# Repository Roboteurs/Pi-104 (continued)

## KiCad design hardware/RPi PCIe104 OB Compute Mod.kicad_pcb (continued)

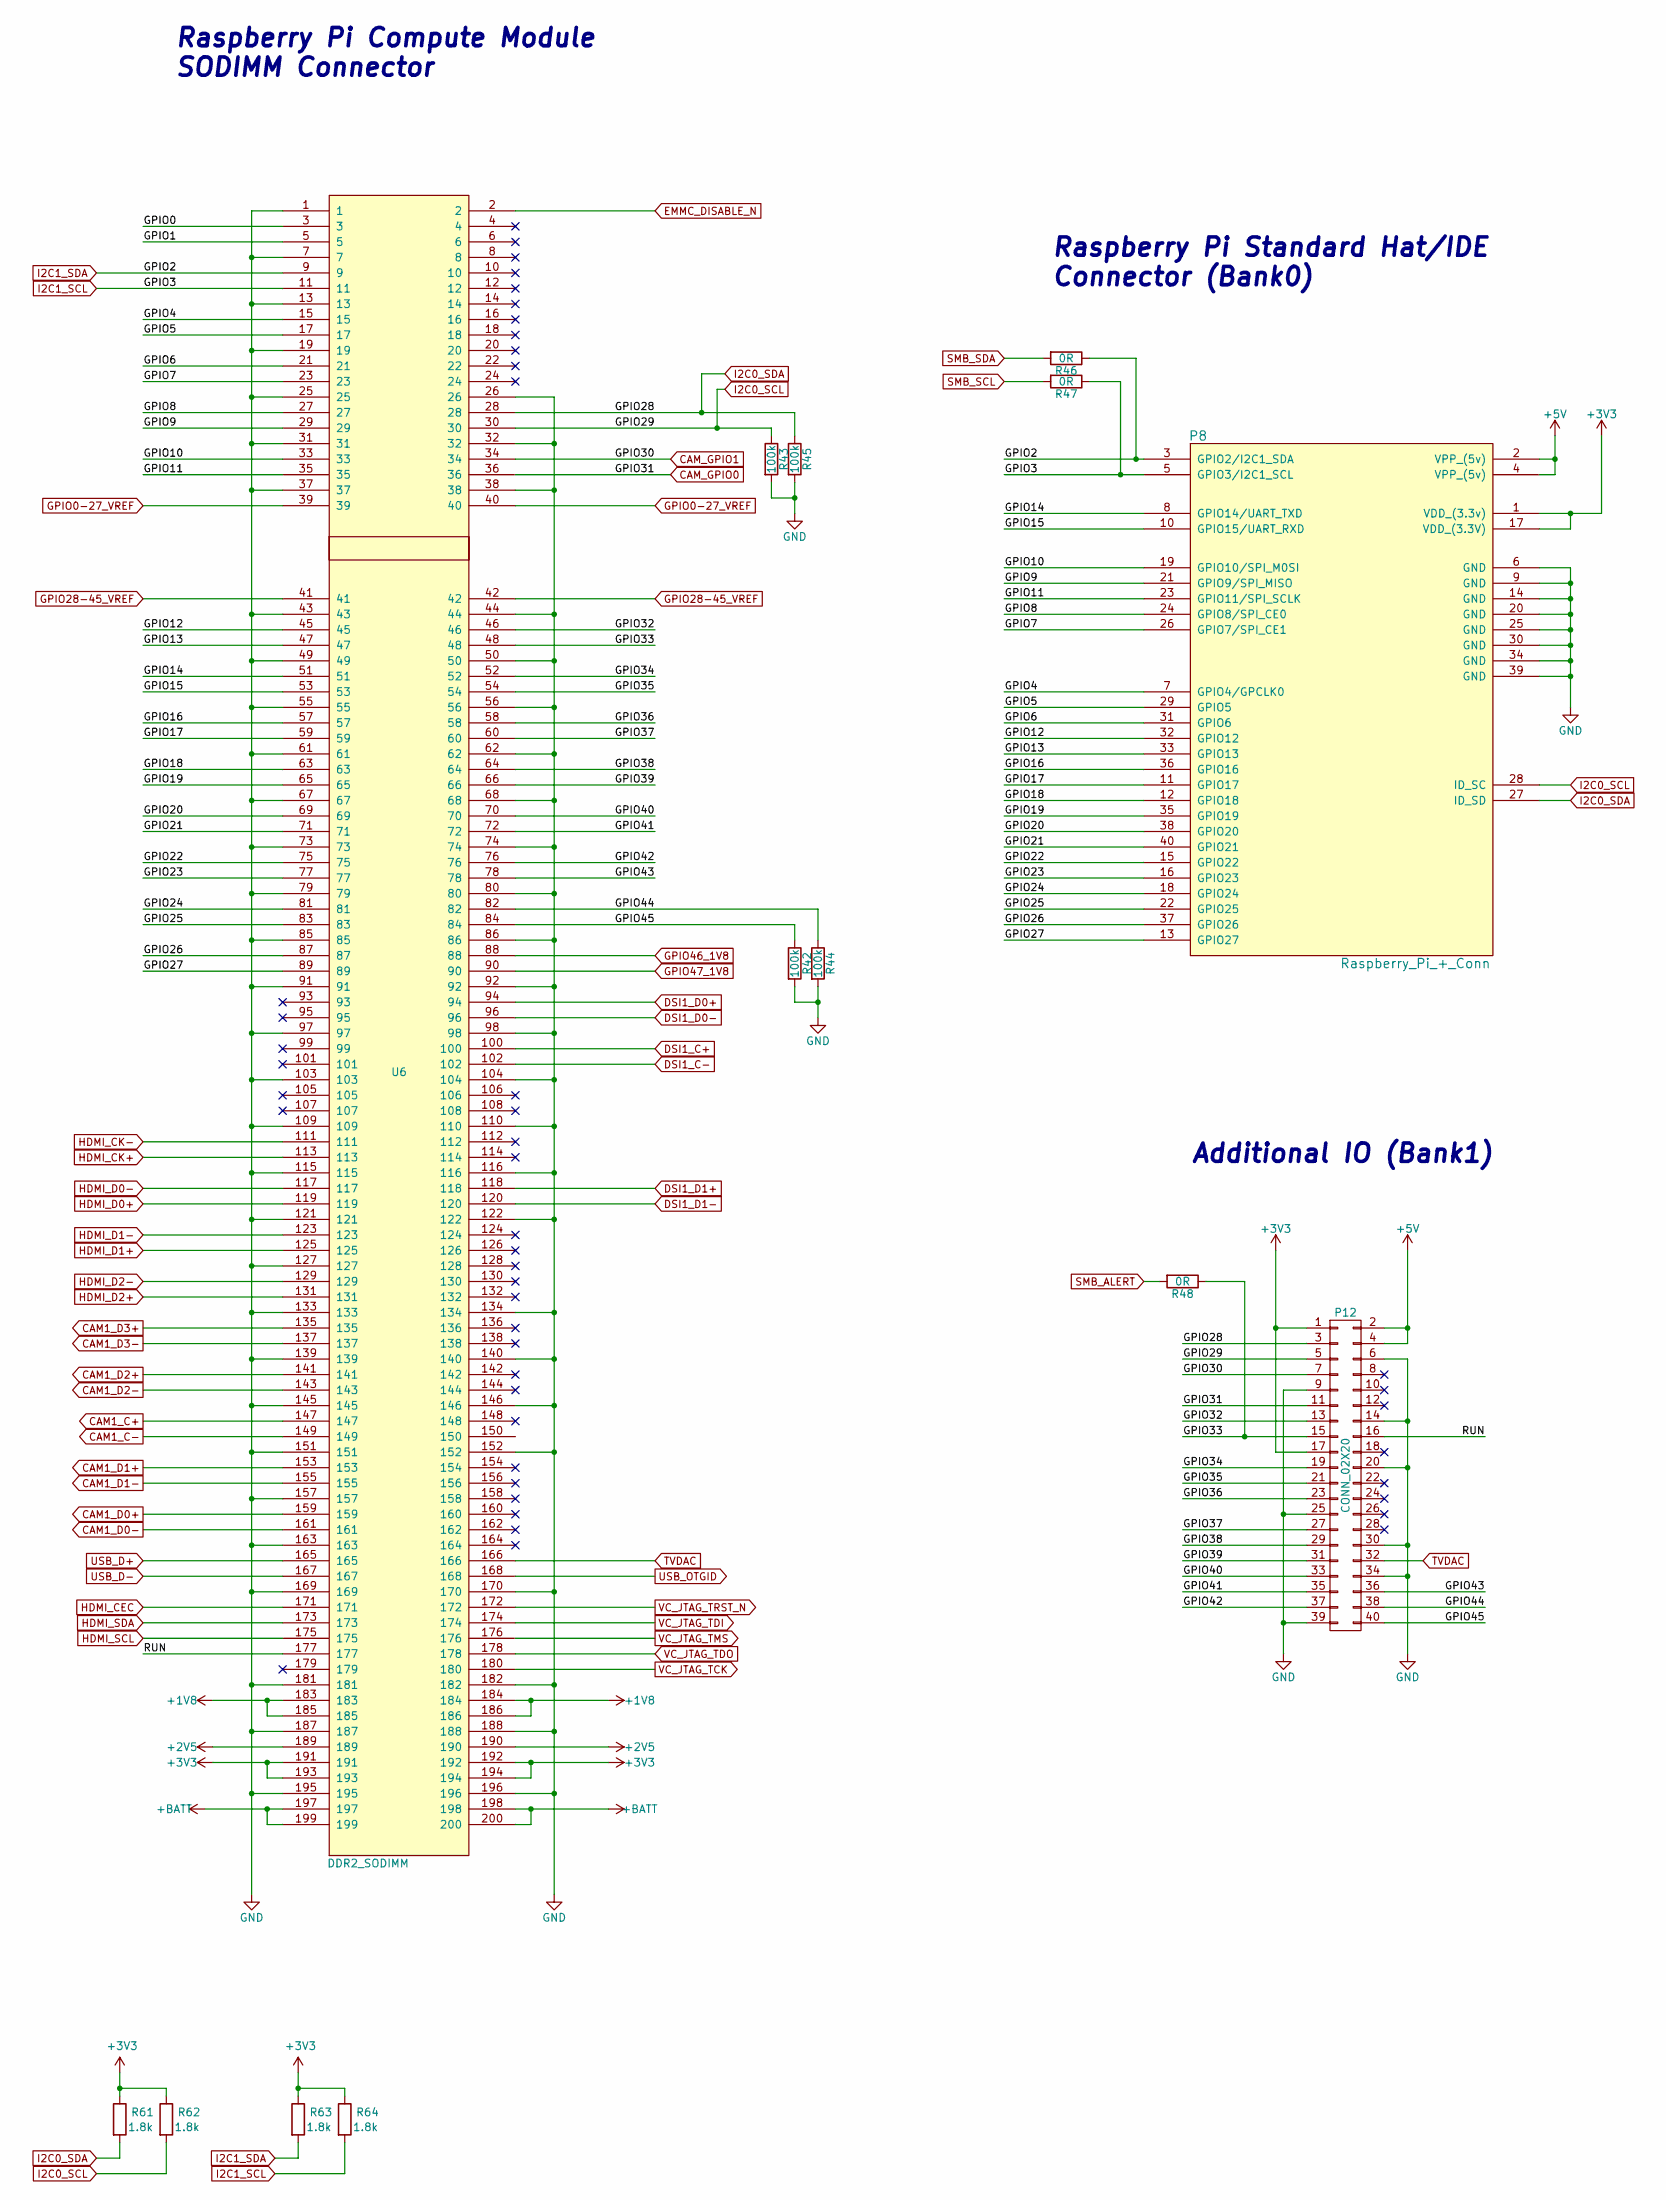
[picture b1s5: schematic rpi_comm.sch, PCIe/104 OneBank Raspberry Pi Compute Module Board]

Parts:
P8: Raspberry_Pi_+_Conn; vasch_strip_20x2; mouser# 517-N2540-6002RB
P12: CONN_02X20; vasch_strip_20x2; mouser# 517-N2540-6002RB
R42, R43, R44, R45: 100k; r_0402; mouser# 667-ERJ-2GEJ104X
R46, R47, R48: 0R; r_0402; mouser# 71-CRCW0402-0-E3
R61, R62, R63, R64: 1.8k; r_0402; mouser# 667-ERJ-2GEJ182X
U6: DDR2_SODIMM; Socket_SODIMM_DDR1-2_TE_1612618_Debug; mouser# 571-1612618-4

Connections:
+1V8: U6.183, U6.184, U6.185, U6.186; also elsewhere on the board
+2V5: U6.189, U6.190; also elsewhere on the board
+3V3: P8.1 (VDD_(3.3v)), P8.17 (VDD_(3.3V)), P12.1, P12.17, R61.1, R62.1, R63.1, R64.1, U6.191, U6.192, U6.193, U6.194; also elsewhere on the board
+5V: P8.2 (VPP_(5v)), P8.4 (VPP_(5v)), P12.2, P12.4; also elsewhere on the board
+BATT: U6.197, U6.198, U6.199, U6.200; also elsewhere on the board
/Raspberry Pi Mod & I/O/GPIO0: U6.3
/Raspberry Pi Mod & I/O/GPIO1: U6.5
/Raspberry Pi Mod & I/O/GPIO4: P8.7 (GPIO4/GPCLK0), U6.15
/Raspberry Pi Mod & I/O/GPIO5: P8.29 (GPIO5), U6.17
/Raspberry Pi Mod & I/O/GPIO6: P8.31 (GPIO6), U6.21
/Raspberry Pi Mod & I/O/GPIO7: P8.26 (GPIO7/SPI_CE1), U6.23
/Raspberry Pi Mod & I/O/GPIO8: P8.24 (GPIO8/SPI_CE0), U6.27
/Raspberry Pi Mod & I/O/GPIO9: P8.21 (GPIO9/SPI_MISO), U6.29
/Raspberry Pi Mod & I/O/GPIO10: P8.19 (GPIO10/SPI_M0SI), U6.33
/Raspberry Pi Mod & I/O/GPIO11: P8.23 (GPIO11/SPI_SCLK), U6.35
/Raspberry Pi Mod & I/O/GPIO12: P8.32 (GPIO12), U6.45
/Raspberry Pi Mod & I/O/GPIO13: P8.33 (GPIO13), U6.47
/Raspberry Pi Mod & I/O/GPIO14: P8.8 (GPIO14/UART_TXD), U6.51
/Raspberry Pi Mod & I/O/GPIO15: P8.10 (GPIO15/UART_RXD), U6.53
/Raspberry Pi Mod & I/O/GPIO16: P8.36 (GPIO16), U6.57
/Raspberry Pi Mod & I/O/GPIO17: P8.11 (GPIO17), U6.59
/Raspberry Pi Mod & I/O/GPIO18: P8.12 (GPIO18), U6.63
/Raspberry Pi Mod & I/O/GPIO19: P8.35 (GPIO19), U6.65
/Raspberry Pi Mod & I/O/GPIO20: P8.38 (GPIO20), U6.69
/Raspberry Pi Mod & I/O/GPIO21: P8.40 (GPIO21), U6.71
/Raspberry Pi Mod & I/O/GPIO22: P8.15 (GPIO22), U6.75
/Raspberry Pi Mod & I/O/GPIO23: P8.16 (GPIO23), U6.77
/Raspberry Pi Mod & I/O/GPIO24: P8.18 (GPIO24), U6.81
/Raspberry Pi Mod & I/O/GPIO25: P8.22 (GPIO25), U6.83
/Raspberry Pi Mod & I/O/GPIO26: P8.37 (GPIO26), U6.87
/Raspberry Pi Mod & I/O/GPIO27: P8.13 (GPIO27), U6.89
/Raspberry Pi Mod & I/O/GPIO32: P12.13, U6.46
/Raspberry Pi Mod & I/O/GPIO33: P12.15, R48.1, U6.48
/Raspberry Pi Mod & I/O/GPIO34: P12.19, U6.52
/Raspberry Pi Mod & I/O/GPIO35: P12.21, U6.54
/Raspberry Pi Mod & I/O/GPIO36: P12.23, U6.58
/Raspberry Pi Mod & I/O/GPIO37: P12.27, U6.60
/Raspberry Pi Mod & I/O/GPIO38: P12.29, U6.64
/Raspberry Pi Mod & I/O/GPIO39: P12.31, U6.66
/Raspberry Pi Mod & I/O/GPIO40: P12.33, U6.70
/Raspberry Pi Mod & I/O/GPIO41: P12.35, U6.72
/Raspberry Pi Mod & I/O/GPIO42: P12.37, U6.76
/Raspberry Pi Mod & I/O/GPIO43: P12.36, U6.78
/Raspberry Pi Mod & I/O/GPIO44: P12.38, R44.1, U6.82
/Raspberry Pi Mod & I/O/GPIO45: P12.40, R42.1, U6.84
/Raspberry Pi Mod & I/O/RUN: P12.16, U6.177
CAM1_C+: U6.147; also elsewhere on the board
CAM1_C-: U6.149; also elsewhere on the board
CAM1_D0+: U6.159; also elsewhere on the board
CAM1_D0-: U6.161; also elsewhere on the board
CAM1_D1+: U6.153; also elsewhere on the board
CAM1_D1-: U6.155; also elsewhere on the board
CAM1_D2+: U6.141
CAM1_D2-: U6.143
CAM1_D3+: U6.135
CAM1_D3-: U6.137
CAM_GPIO0: P12.11, U6.36; also elsewhere on the board
CAM_GPIO1: P12.7, U6.34; also elsewhere on the board
DSI1_C+: U6.100; also elsewhere on the board
DSI1_C-: U6.102; also elsewhere on the board
DSI1_D0+: U6.94; also elsewhere on the board
DSI1_D0-: U6.96; also elsewhere on the board
DSI1_D1+: U6.118; also elsewhere on the board
DSI1_D1-: U6.120; also elsewhere on the board
EMMC_DISABLE_N: U6.2; also elsewhere on the board
GND: P8.6 (GND), P8.9 (GND), P8.14 (GND), P8.20 (GND), P8.25 (GND), P8.30 (GND), P8.34 (GND), P8.39 (GND), P12.6, P12.9, P12.14, P12.20, P12.25, P12.30, P12.34, P12.39, R42.2, R43.2, R44.2, R45.2, U6.1, U6.7, U6.13, U6.19, U6.25, U6.26, U6.31, U6.32, U6.37, U6.38, U6.43, U6.44, U6.49, U6.50, U6.55, U6.56, U6.61, U6.62, U6.67, U6.68, U6.73, U6.74, U6.79, U6.80, U6.85, U6.86, U6.91, U6.92, U6.97, U6.98, U6.103, U6.104, U6.109, U6.110, U6.115, U6.116, U6.121, U6.122, U6.127, U6.133, U6.134, U6.139, U6.140, U6.145, U6.146, U6.151, U6.152, U6.157, U6.163, U6.169, U6.170, U6.181, U6.182, U6.187, U6.188, U6.195, U6.196; also elsewhere on the board
GPIO0-27_VREF: U6.39, U6.40; also elsewhere on the board
GPIO28-45_VREF: U6.41, U6.42; also elsewhere on the board
GPIO46_1V8: U6.88; also elsewhere on the board
GPIO47_1V8: U6.90; also elsewhere on the board
HDMI_CEC: U6.171; also elsewhere on the board
HDMI_CK+: U6.113; also elsewhere on the board
HDMI_CK-: U6.111; also elsewhere on the board
HDMI_D0+: U6.119; also elsewhere on the board
HDMI_D0-: U6.117; also elsewhere on the board
HDMI_D1+: U6.125; also elsewhere on the board
HDMI_D1-: U6.123; also elsewhere on the board
HDMI_D2+: U6.131; also elsewhere on the board
HDMI_D2-: U6.129; also elsewhere on the board
HDMI_SCL: U6.175; also elsewhere on the board
HDMI_SDA: U6.173; also elsewhere on the board
I2C0_SCL: P8.28 (ID_SC), P12.5, R43.1, R62.2, U6.30; also elsewhere on the board
I2C0_SDA: P8.27 (ID_SD), P12.3, R45.1, R61.2, U6.28; also elsewhere on the board
I2C1_SCL: P8.5 (GPIO3/I2C1_SCL), R47.1, R64.2, U6.11
I2C1_SDA: P8.3 (GPIO2/I2C1_SDA), R46.1, R63.2, U6.9
SMB_ALERT: R48.2; also elsewhere on the board
SMB_SCL: R47.2; also elsewhere on the board
SMB_SDA: R46.2; also elsewhere on the board
TVDAC: P12.32, U6.166
USB_D+: U6.165; also elsewhere on the board
USB_D-: U6.167; also elsewhere on the board
USB_OTGID: U6.168; also elsewhere on the board
VC_JTAG_TCK: U6.180
VC_JTAG_TDI: U6.174
VC_JTAG_TDO: U6.178
VC_JTAG_TMS: U6.176
VC_JTAG_TRST_N: U6.172

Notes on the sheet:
Raspberry Pi Compute Module SODIMM Connector
Raspberry Pi Standard Hat/IDE Connector (Bank0)
Additional IO (Bank1)

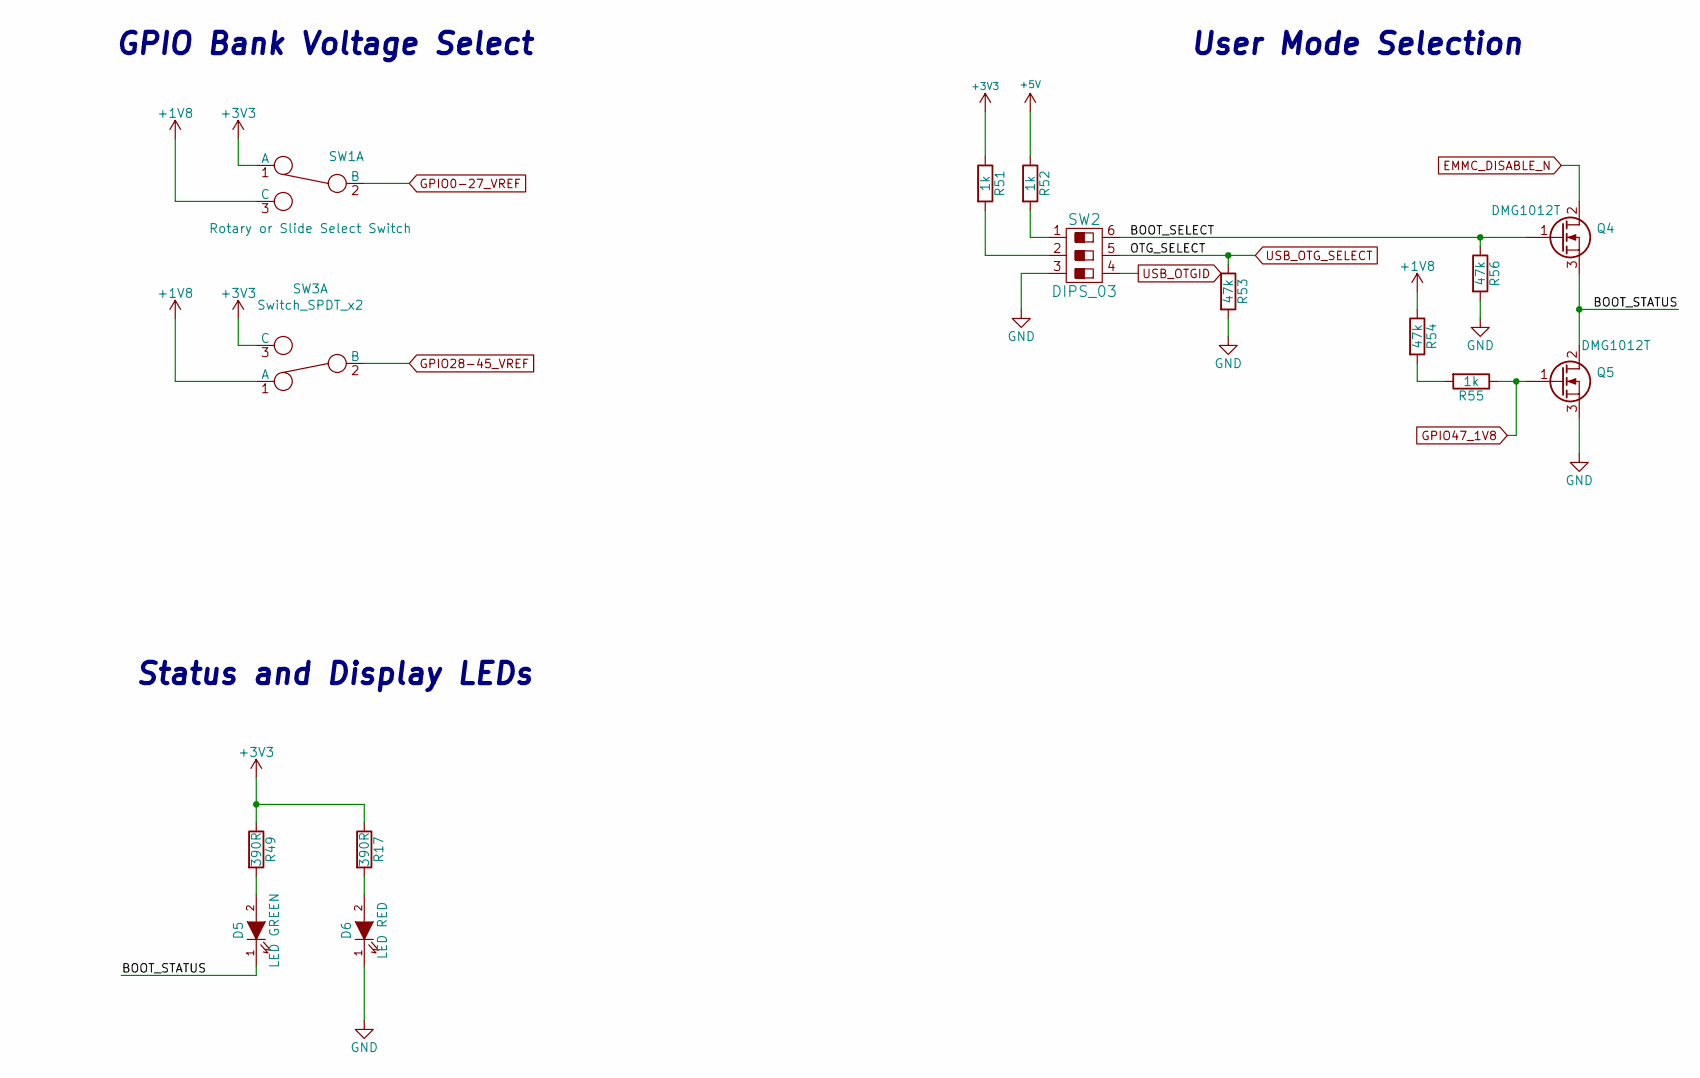
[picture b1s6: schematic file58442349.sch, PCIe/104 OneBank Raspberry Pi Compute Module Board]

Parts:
D5: LED GREEN; Led_0603; mouser# 743-HT-191YG
D6: LED RED; Led_0603; mouser# 743-HT-191USD
Q4, Q5: DMG1012T; SOT523; mouser# 621-DMG1012T-7
R17, R49: 390R; r_0402; mouser# 667-ERJ-2RKF3900X
R51, R52, R55: 1k; r_0402; mouser# 71-CRCW0402-1.0K-E3
R53, R54, R56: 47k; r_0402; mouser# 71-CRCW0402-47K-E3
SW1: Rotary or Slide Select Switch; SSSS820201; mouser# 688-SSSS820201
SW2: DIPS_03; ADF03S04; mouser# 506-ADF03S04
SW3: Switch_SPDT_x2; SSSS820201; mouser# 688-SSSS820201

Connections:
+1V8: R54.1, SW1.3 (C), SW3.1 (A); also elsewhere on the board
+3V3: R17.1, R49.1, R51.1, SW1.1 (A), SW3.3 (C); also elsewhere on the board
+5V: R52.1; also elsewhere on the board
/User Features & Misc./BOOT_SELECT: Q4.1 (G), R56.1, SW2.6
/User Features & Misc./BOOT_STATUS: D5.1 (K), Q4.3 (S), Q5.2 (D)
EMMC_DISABLE_N: Q4.2 (D); also elsewhere on the board
GND: D6.1 (K), Q5.3 (S), R53.2, R56.2, SW2.3; also elsewhere on the board
GPIO0-27_VREF: SW1.2 (B); also elsewhere on the board
GPIO28-45_VREF: SW3.2 (B); also elsewhere on the board
GPIO47_1V8: Q5.1 (G), R55.1; also elsewhere on the board
unnamed: D5.2 (A), R49.2
unnamed: D6.2 (A), R17.2
unnamed: R51.2, SW2.2
unnamed: R52.2, SW2.1
unnamed: R54.2, R55.2
USB_OTGID: SW2.4; also elsewhere on the board
USB_OTG_SELECT: R53.1, SW2.5; also elsewhere on the board

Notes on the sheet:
GPIO Bank Voltage Select
User Mode Selection
Status and Display LEDs

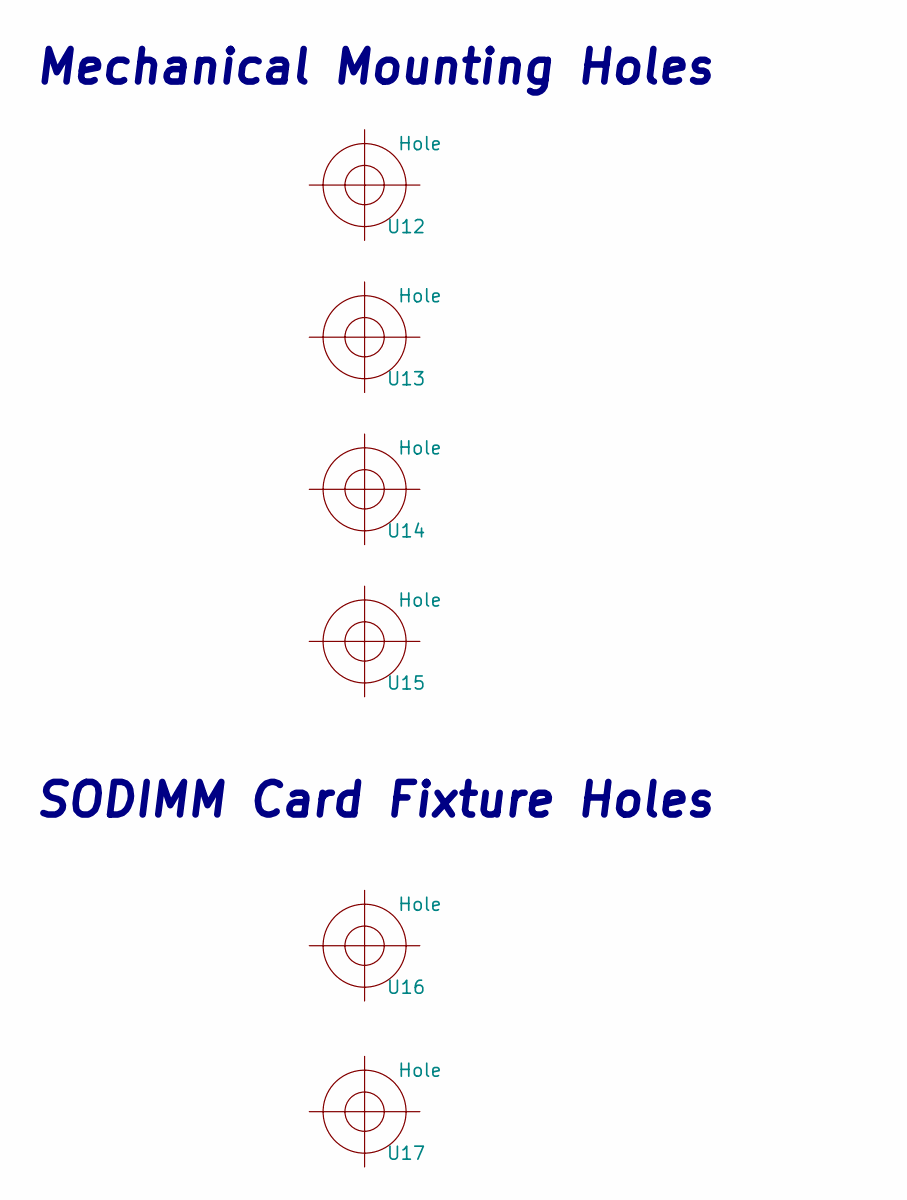
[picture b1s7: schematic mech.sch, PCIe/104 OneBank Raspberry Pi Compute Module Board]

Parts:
U12, U13, U14, U15, U16, U17: Hole

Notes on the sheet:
Mechanical Mounting Holes
SODIMM Card Fixture Holes

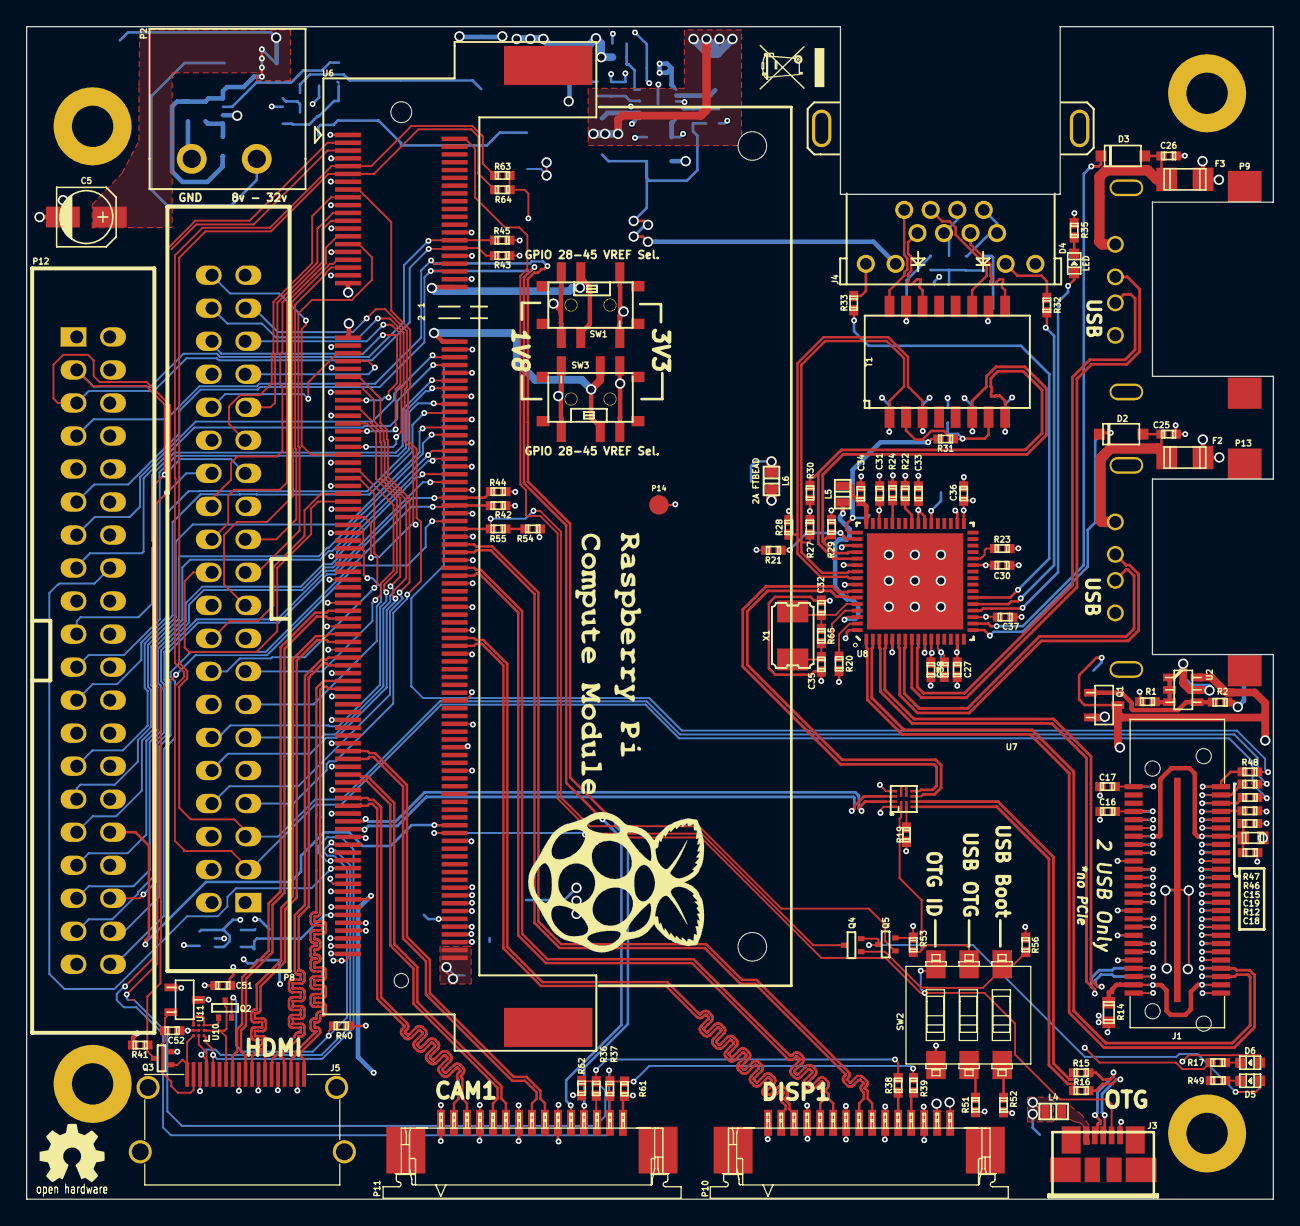
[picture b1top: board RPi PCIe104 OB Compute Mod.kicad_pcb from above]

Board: 4 copper layers, 95.9 x 90.2 mm, 173 parts (0 on the bottom side), 201 nets.

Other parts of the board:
H1, H2, H3, H4: PCB_HOLE; PCIE104_HOLE

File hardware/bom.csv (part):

Reference, Value, Footprint, manf#, mouser#
U4,LM3489,w_smd_dil:msoic-8,LM3489MM/NOPB,926-LM3489MM/NOPB
R4,24k,w_smd_resistors:r_0402,ERJ-2GEJ243X,667-ERJ-2GEJ243X
C7,0.1uf/50V,w_smd_resistors:r_0402,GRM155R71H104KE14J,81-GRM155R71H104KE4J
C5,4.7uf/50V,w_smd_cap:c_elec_4x5.7,EMVA500ADA4R7MD55G,661-EMVA500ADA4R7MD5
C8,1nf/50V,w_smd_resistors:r_0402,GRM1555C1H102JA01D,81-GRM1555C1H102JA1D
R5,240,w_smd_resistors:r_0603,ESR03EZPJ241,755-ESR03EZPJ241
D1,0.6V,w_smd_diode:do214aa,MBRS140,512-MBRS140
L3,22uH/2.2A/100mO,w_smd_inductors:inductor_smd_8x5mm,SRN8040-220M,652-SRN8040-220M
R9,30k,w_smd_resistors:r_0402,ERJ-2RKF3002X,667-ERJ-2RKF3002X
R10,10k,w_smd_resistors:r_0402,ERJ-2GEJ103X,667-ERJ-2GEJ103X
U5,FDC5614P,w_smd_trans:sot23-6,FDC5614P,512-FDC5614P 
F1,2A,w_smd_resistors:r_1206,MF-NSMF200-2,652-MF-NSMF200-2
C10,0.1uf/50V,w_smd_resistors:r_0402,GRM155R71H104KE14J,81-GRM155R71H104KE4J
U3,PAM2306A,w_smd_qfn:dfn12,PAM2306AYPKE,621-PAM2306AYPKE
L2,4.7uH/2A/107mR,Inductors:Inductor_Taiyo-Yuden_MD-4040,MDWK4040T4R7MM,963-MDWK4040T4R7MM
C11,DNP,w_smd_cap:c_0402,-,-
R7,0R,w_smd_resistors:r_0402,CRCW04020000Z0ED,71-CRCW0402-0-E3
C12,DNP,w_smd_cap:c_0402,-,-
R8,DNP,w_smd_resistors:r_0402,-,-
R11,DNP,w_smd_resistors:r_0402,-,-
R3,100k,w_smd_resistors:r_0402,ERJ-2GEJ104X,667-ERJ-2GEJ104X
C4,100nf/50V,w_smd_cap:c_0402,GRM155R71H104KE14J,81-GRM155R71H104KE4J
C6,10uf/10V,w_smd_cap:c_0805,GRM21BR71A106KE51L,81-GRM21BR71A106KE51
U2,dmmt5401,w_smd_trans:sot23-6,DMMT5401-7-F,621-DMMT5401-7-F
R2,47k,w_smd_resistors:r_0402,CRCW040247K0FKED,71-CRCW0402-47K-E3
R1,10k,w_smd_resistors:r_0402,ERJ-2GEJ103X,667-ERJ-2GEJ103X
Q1,DMG2305UX,w_smd_trans:sot23,DMG2305UX-7,621-DMG2305UX-7
U1,AP7115,w_smd_trans:sot323-5,AP7115-25SEG-7,621-AP7115-25SEG-7
C1,1uf/6V,w_smd_resistors:r_0402,GRM155R70J105KA12J,81-GRM155R70J105KA2J
C2,100nf/50V,w_smd_resistors:r_0402,GRM155R71H104KE14J,81-GRM155R71H104KE4J
C3,4.7uf6.3V,w_smd_cap:c_0402,04026D475KAT2A,581-04026D475KAT2A
P2,Industrial Power Screw Terminal,project_foot:796644-2,571-796644-2,571-796644-2
P1,TST,Measurement_Points:Measurement_Point_Round-SMD-Pad_Small,-,-
C20,47uf/10V,w_smd_cap:c_1210,C1210C476M8PACTU,80-C1210C476M8P
R13,0R,w_smd_resistors:r_0402,CRCW04020000Z0ED,71-CRCW0402-0-E3
C9,10uf/10V,w_smd_cap:c_0805,GRM21BR71A106KE51L,81-GRM21BR71A106KE51
R6,0R,w_smd_resistors:r_0402,CRCW04020000Z0ED,71-CRCW0402-0-E3
C13,10uf/10V,w_smd_cap:c_0805,GRM21BR71A106KE51L,81-GRM21BR71A106KE51
C14,10uf/10V,w_smd_cap:c_0805,GRM21BR71A106KE51L,81-GRM21BR71A106KE51
L1,4.7uH/2A/107mR,Inductors:Inductor_Taiyo-Yuden_MD-4040,MDWK4040T4R7MM,963-MDWK4040T4R7MM
C21,47uf/10V,w_smd_cap:c_1210,C1210C476M8PACTU,80-C1210C476M8P
C22,47uf/10V,w_smd_cap:c_1210,C1210C476M8PACTU,80-C1210C476M8P
P3,TST,Measurement_Points:Measurement_Point_Round-SMD-Pad_Small,-,-
P4,TST,Measurement_Points:Measurement_Point_Round-SMD-Pad_Small,-,-
P5,TST,Measurement_Points:Measurement_Point_Round-SMD-Pad_Small,-,-
P6,TST,Measurement_Points:Measurement_Point_Round-SMD-Pad_Small,-,-
P7,TST,Measurement_Points:Measurement_Point_Round-SMD-Pad_Small,-,-
D9,SMBJ5.0A,w_smd_diode:do214aa,SMBJ5.0A,576-SMBJ5.0A
D8,SMBJ5.0A,w_smd_diode:do214aa,SMBJ5.0A,576-SMBJ5.0A
P14,TST,Measurement_Points:Measurement_Point_Round-SMD-Pad_Small,-,-
J2,OneBank,project_foot:ASP-129646-22,ASP-129646-22,-
J1,OneBank,project_foot:ASP-129637-13,ASP-129637-13,-
R12,DNP,w_smd_resistors:r_0402,-,-
C18,10nf/50V,w_smd_cap:c_0402,04025C103KAT2A,581-04025C103KAT2A
C19,10nf/50V,w_smd_cap:c_0402,04025C103KAT2A,581-04025C103KAT2A
C15,10nf/50V,w_smd_cap:c_0402,04025C103KAT2A,581-04025C103KAT2A
R14,DNP,w_smd_resistors:r_0603,-,-
C16,10nf/50V,w_smd_cap:c_0402,04025C103KAT2A,581-04025C103KAT2A
C17,10nf/50V,w_smd_cap:c_0402,04025C103KAT2A,581-04025C103KAT2A
U8,LAN9514I-JZX,project_foot:QFN50P900X900X100-65N,LAN9514I-JZX,886-LAN9514I-JZX 
U7,TS3USB3031,project_foot:PWQFN-N12,TS3USB3031RMGR,595-TS3USB3031RMGR
R19,10k,w_smd_resistors:r_0402,ERJ-2GEJ103X,667-ERJ-2GEJ103X
X1,25.000MHz,w_crystal:crystal_smd_5x3.2mm,ABM3-25.000MHZ-B2-T,815-ABM3-25-B2-T
C32,27pf,w_smd_cap:c_0402,04025A270FAT2A,581-04025A270FAT2A
C35,27pf,w_smd_cap:c_0402,04025A270FAT2A,581-04025A270FAT2A
L5,2A FTBEAD,w_smd_inductors:inductor_smd_0603,BLM18PG121SN1D,81-BLM18PG121SN1D
C28,0.1uf/50V,w_smd_cap:c_0402,GRM155R71H104KE14J,81-GRM155R71H104KE4J
C34,0.1uf/50V,w_smd_cap:c_0402,GRM155R71H104KE14J,81-GRM155R71H104KE4J
C29,0.1uf/50V,w_smd_cap:c_0402,GRM155R71H104KE14J,81-GRM155R71H104KE4J
C31,0.1uf/50V,w_smd_cap:c_0402,GRM155R71H104KE14J,81-GRM155R71H104KE4J
C33,0.1uf/50V,w_smd_cap:c_0402,GRM155R71H104KE14J,81-GRM155R71H104KE4J
C36,0.1uf/50V,w_smd_cap:c_0402,GRM155R71H104KE14J,81-GRM155R71H104KE4J
C37,0.1uf/50V,w_smd_cap:c_0402,GRM155R71H104KE14J,81-GRM155R71H104KE4J
C38,0.1uf/50V,w_smd_cap:c_0402,GRM155R71H104KE14J,81-GRM155R71H104KE4J
L6,2A FTBEAD,w_smd_inductors:inductor_smd_0603,BLM18PG121SN1D,81-BLM18PG121SN1D
C39,0.1uf/50V,w_smd_cap:c_0402,GRM155R71H104KE14J,81-GRM155R71H104KE4J
C40,0.1uf/50V,w_smd_cap:c_0402,GRM155R71H104KE14J,81-GRM155R71H104KE4J
C41,0.1uf/50V,w_smd_cap:c_0402,GRM155R71H104KE14J,81-GRM155R71H104KE4J
C42,0.1uf/50V,w_smd_cap:c_0402,GRM155R71H104KE14J,81-GRM155R71H104KE4J
C43,0.1uf/50V,w_smd_cap:c_0402,GRM155R71H104KE14J,81-GRM155R71H104KE4J
C44,0.1uf/50V,w_smd_cap:c_0402,GRM155R71H104KE14J,81-GRM155R71H104KE4J
R20,12k,w_smd_resistors:r_0402,CPF0402B12KE1,279-CPF0402B12KE1
R23,10k,w_smd_resistors:r_0402,ERJ-2GEJ103X,667-ERJ-2GEJ103X
R27,49.9R,w_smd_resistors:r_0402,RG1005P-49R9-B-T5,754-RG1005P-49R9-BT5
R28,49.9R,w_smd_resistors:r_0402,RG1005P-49R9-B-T5,754-RG1005P-49R9-BT5
R29,49.9R,w_smd_resistors:r_0402,RG1005P-49R9-B-T5,754-RG1005P-49R9-BT5
R30,49.9R,w_smd_resistors:r_0402,RG1005P-49R9-B-T5,754-RG1005P-49R9-BT5
R31,10R,w_smd_resistors:r_0402,RK73H1ERTTP10R0F,660-RK73H1ERTTP10R0F
C45,0.022uf/50V,w_smd_cap:c_0402,0402YC223KAT4A,581-0402YC223KAT4A
R32,390R,w_smd_resistors:r_0402,ERJ-2RKF3900X,667-ERJ-2RKF3900X
R33,390R,w_smd_resistors:r_0402,ERJ-2RKF3900X,667-ERJ-2RKF3900X
D4,LED,w_smd_leds:Led_0603,HT-191YG-5310,743-HT-191YG
R35,390R,w_smd_resistors:r_0402,ERJ-2RKF3900X,667-ERJ-2RKF3900X
C46,15pf/50V,w_smd_cap:c_0402,GRM1555C1H150JA01D,81-GRM1555C1H150JA1D
C47,15pf/50V,w_smd_cap:c_0402,GRM1555C1H150JA01D,81-GRM1555C1H150JA1D
C49,15pf/50V,w_smd_cap:c_0402,GRM1555C1H150JA01D,81-GRM1555C1H150JA1D
C50,15pf/50V,w_smd_cap:c_0402,GRM1555C1H150JA01D,81-GRM1555C1H150JA1D
R22,10k,w_smd_resistors:r_0402,ERJ-2GEJ103X,667-ERJ-2GEJ103X
R21,10k,w_smd_resistors:r_0402,ERJ-2GEJ103X,667-ERJ-2GEJ103X
J3,MICRO_USB,w_conn_pc:conn_usb_B_micro_smd-2,47346-0001,538-47346-0001
R24,10k,w_smd_resistors:r_0402,ERJ-2GEJ103X,667-ERJ-2GEJ103X
R16,47R,w_smd_resistors:r_0402,RG1005P-470-D-T10,754-RG1005P-470DT10
R15,47R,w_smd_resistors:r_0402,RG1005P-470-D-T10,754-RG1005P-470DT10
L4,2A FTBEAD,w_smd_inductors:inductor_smd_0603,BLM18PG121SN1D,81-BLM18PG121SN1D
D2,BAS16D,w_smd_diode:sod123,BAS16D-E3-08,78-BAS16D-E3-08
C25,100n/50V,w_smd_cap:c_0402,GRM155R71H104KE14J,81-GRM155R71H104KE4J
C26,100n/50V,w_smd_cap:c_0402,GRM155R71H104KE14J,81-GRM155R71H104KE4J
P13,USB_A,project_foot:4825-80002,48258-0002,538-48258-0002
P9,USB_A,project_foot:4825-80002,48258-0002,538-48258-0002
F2,1A,w_smd_resistors:r_1206,MF-NSMF075-2,652-MF-NSMF075-2
F3,1A,w_smd_resistors:r_1206,MF-NSMF075-2,652-MF-NSMF075-2
C24,47uf/10V,w_smd_cap:c_1210,C1210C476M8PACTU,80-C1210C476M8P
D3,BAS16D,w_smd_diode:sod123,BAS16D-E3-08,78-BAS16D-E3-08
C27,4.7uf6.3V,w_smd_cap:c_0402,04026D475KAT2A,581-04026D475KAT2A
C30,4.7uf6.3V,w_smd_cap:c_0402,04026D475KAT2A,581-04026D475KAT2A
T1,H1102,project_foot:H1102,H1102NL,673-H1102NL
J4,RJ45_LEDS,project_foot:RJE72-188,RJE721881411,523-RJE721881411
R59,75R,w_smd_resistors:r_0402,ERJ-2RKF75R0X,667-ERJ-2RKF75R0X
R57,75R,w_smd_resistors:r_0402,ERJ-2RKF75R0X,667-ERJ-2RKF75R0X
R60,75R,w_smd_resistors:r_0402,ERJ-2RKF75R0X,667-ERJ-2RKF75R0X
R58,75R,w_smd_resistors:r_0402,ERJ-2RKF75R0X,667-ERJ-2RKF75R0X
C53,C,w_smd_cap:c_0402,-,-
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
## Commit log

2016-12-19 Initial hardware commit
2016-12-19 removed all conflict files
